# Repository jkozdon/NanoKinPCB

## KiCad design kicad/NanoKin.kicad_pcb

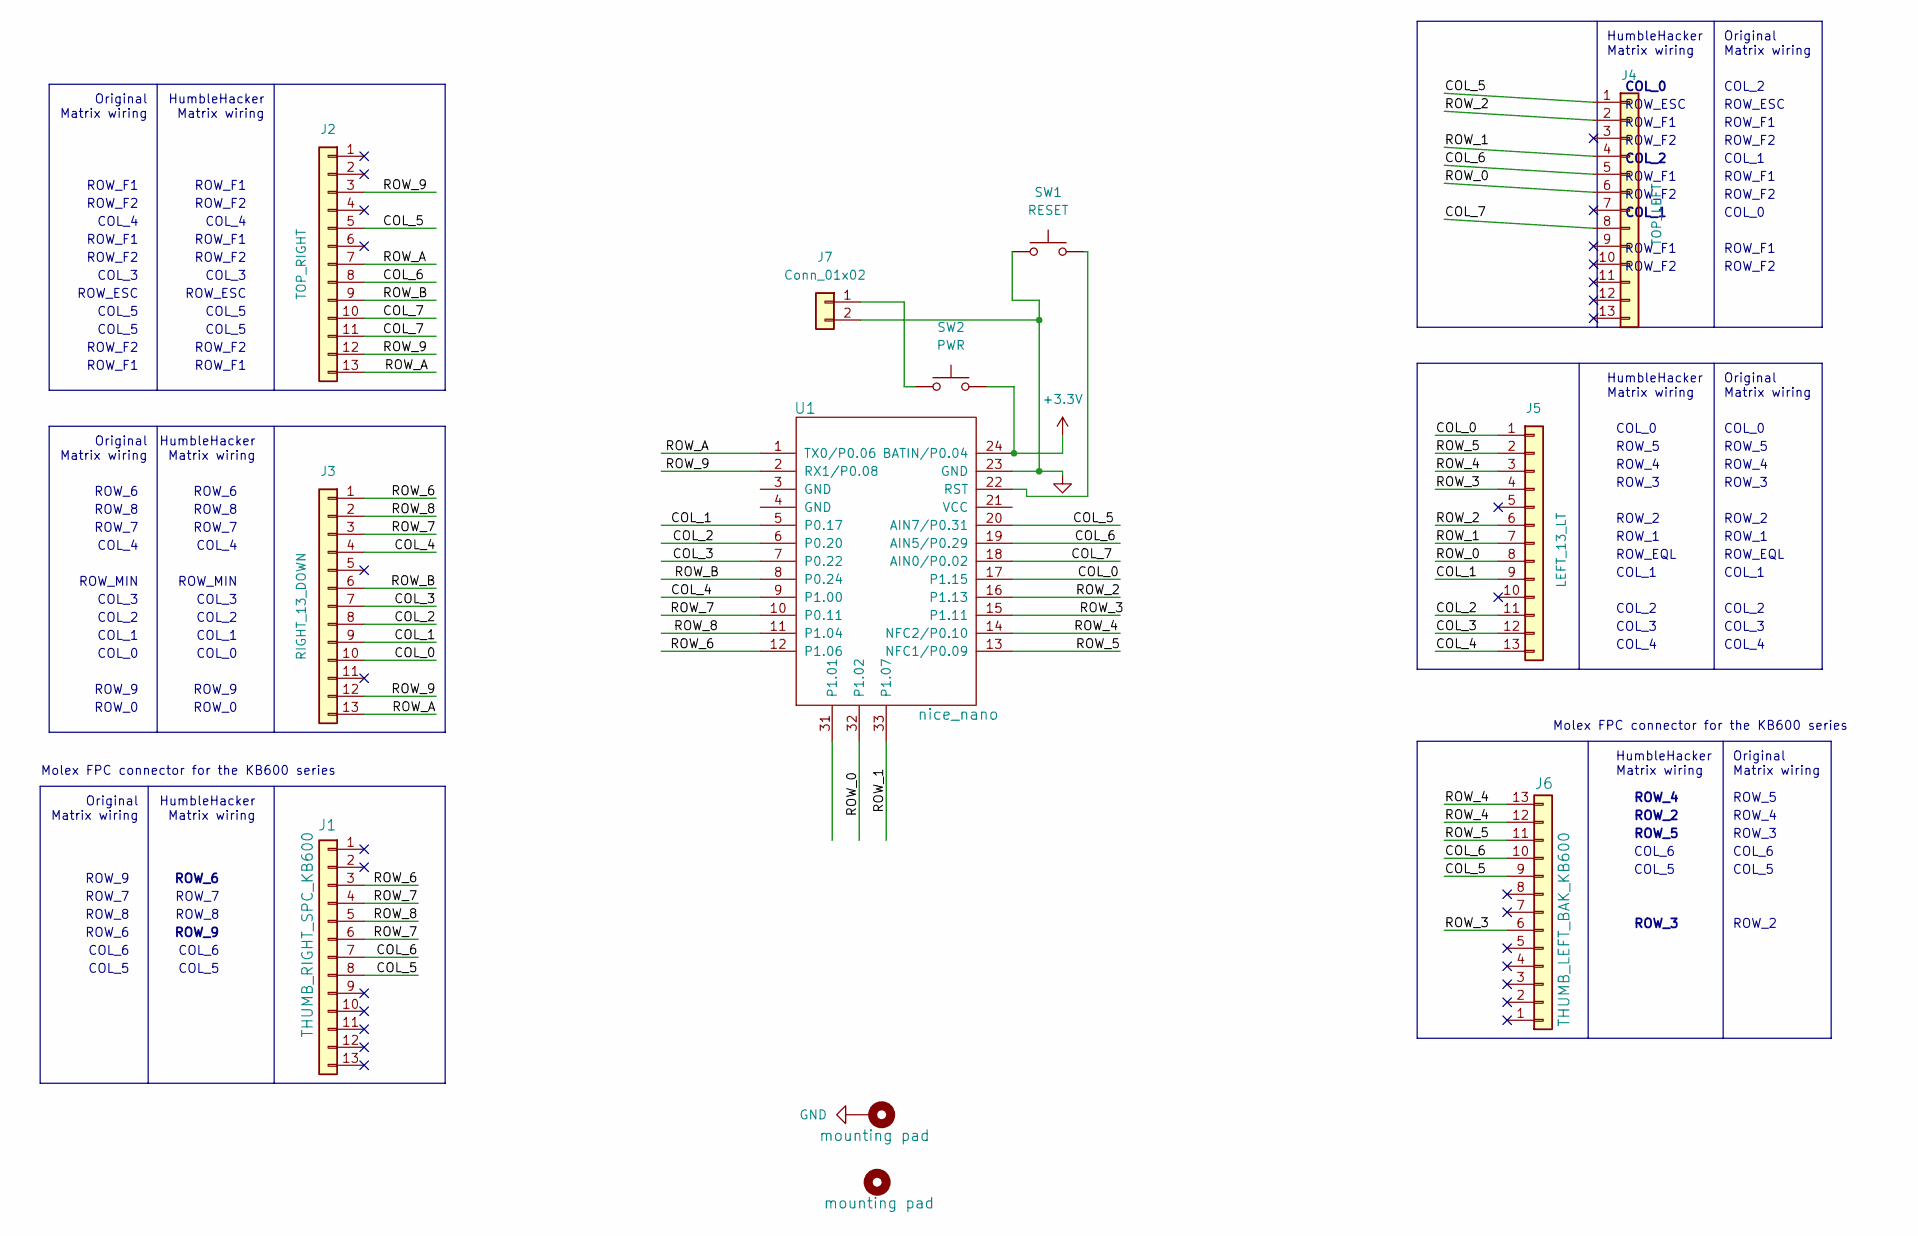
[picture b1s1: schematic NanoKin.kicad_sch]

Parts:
H1: mounting pad; MountingHole_4.3mm_M4_Pad
H2: mounting pad; MountingHole_6mm
J1: THUMB_RIGHT_SPC_KB600; 39-53-2135; MPN 39-53-2135; digikeypn WM14526-ND
J2: TOP_RIGHT; 39-53-2135; MPN 39-53-2135; digikeypn WM14526-ND
J3: RIGHT_13_DOWN; 39-53-2135; MPN 39-53-2135; digikeypn WM14526-ND
J4: TOP_LEFT; 39-53-2135; MPN 39-53-2135; digikeypn WM14526-ND
J5: LEFT_13_LT; 39-53-2135; MPN 39-53-2135; digikeypn WM14526-ND
J6: THUMB_LEFT_BAK_KB600; 39-53-2135; MPN 39-53-2135; digikeypn WM14526-ND
J7: Conn_01x02; bat
SW1: RESET; ResetSW
SW2: PWR; ResetSW
U1: nice_nano

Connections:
+3.3V: SW2.2, U1.24 (BATIN/P0.04)
/COL_0: J3.10, J5.1, U1.17 (P1.15)
/COL_1: J3.9, J5.9, U1.5 (P0.17)
/COL_2: J3.8, J5.11, U1.6 (P0.20)
/COL_3: J3.7, J5.12, U1.7 (P0.22)
/COL_4: J3.4, J5.13, U1.9 (P1.00)
/COL_5: J1.8, J2.5, J4.1, J6.9, U1.20 (AIN7/P0.31)
/COL_6: J1.7, J2.8, J4.5, J6.10, U1.19 (AIN5/P0.29)
/COL_7: J2.10, J2.11, J4.8, U1.18 (AIN0/P0.02)
/ROW_0: J4.6, J5.8, U1.32 (P1.02)
/ROW_1: J4.4, J5.7, U1.33 (P1.07)
/ROW_2: J4.2, J5.6, U1.16 (P1.13)
/ROW_3: J5.4, J6.6, U1.15 (P1.11)
/ROW_4: J5.3, J6.12, J6.13, U1.14 (NFC2/P0.10)
/ROW_5: J5.2, J6.11, U1.13 (NFC1/P0.09)
/ROW_6: J1.3, J3.1, U1.12 (P1.06)
/ROW_7: J1.4, J1.6, J3.3, U1.10 (P0.11)
/ROW_8: J1.5, J3.2, U1.11 (P1.04)
/ROW_9: J2.3, J2.12, J3.12, U1.2 (RX1/P0.08)
/ROW_A: J2.7, J2.13, J3.13, U1.1 (TX0/P0.06)
/ROW_B: J2.9, J3.6, U1.8 (P0.24)
GND: H1.1, J7.2, SW1.1, U1.23 (GND)
unnamed: SW1.2, U1.22 (RST)
unnamed: J7.1, SW2.1

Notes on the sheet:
COL_4
COL_2
COL_6
COL_1
ROW_F2
Original Matrix wiring
ROW_3
ROW_0
ROW_8
COL_3
ROW_2
ROW_F1
ROW_MIN
Molex FPC connector for the KB600 series
ROW_6
COL_5
COL_0
ROW_7
HumbleHacker Matrix wiring
ROW_5
ROW_4
ROW_ESC
ROW_9
ROW_EQL
ROW_1

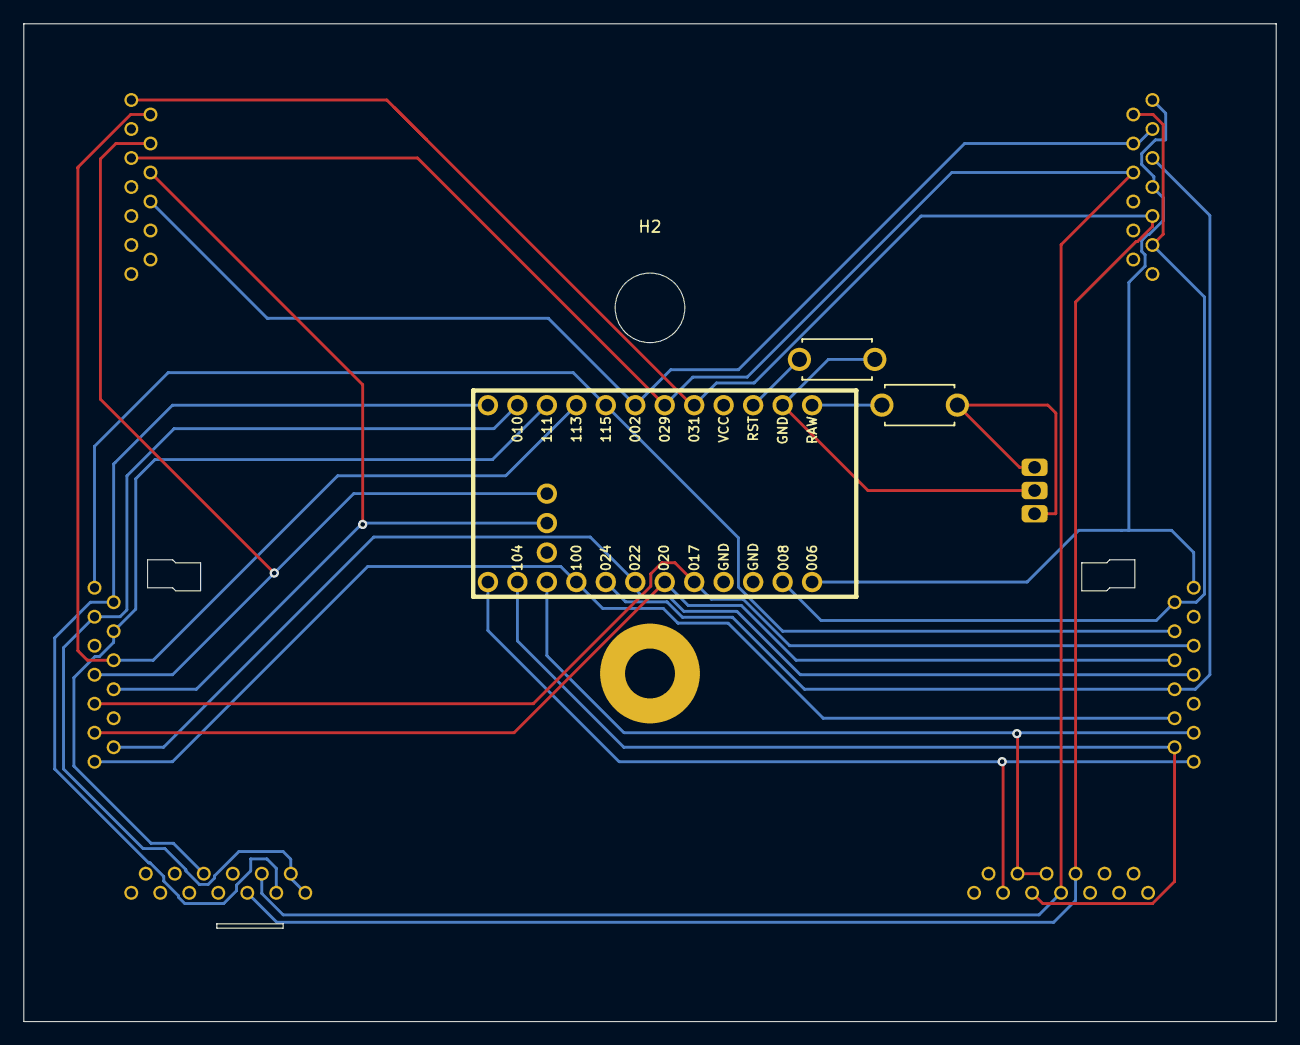
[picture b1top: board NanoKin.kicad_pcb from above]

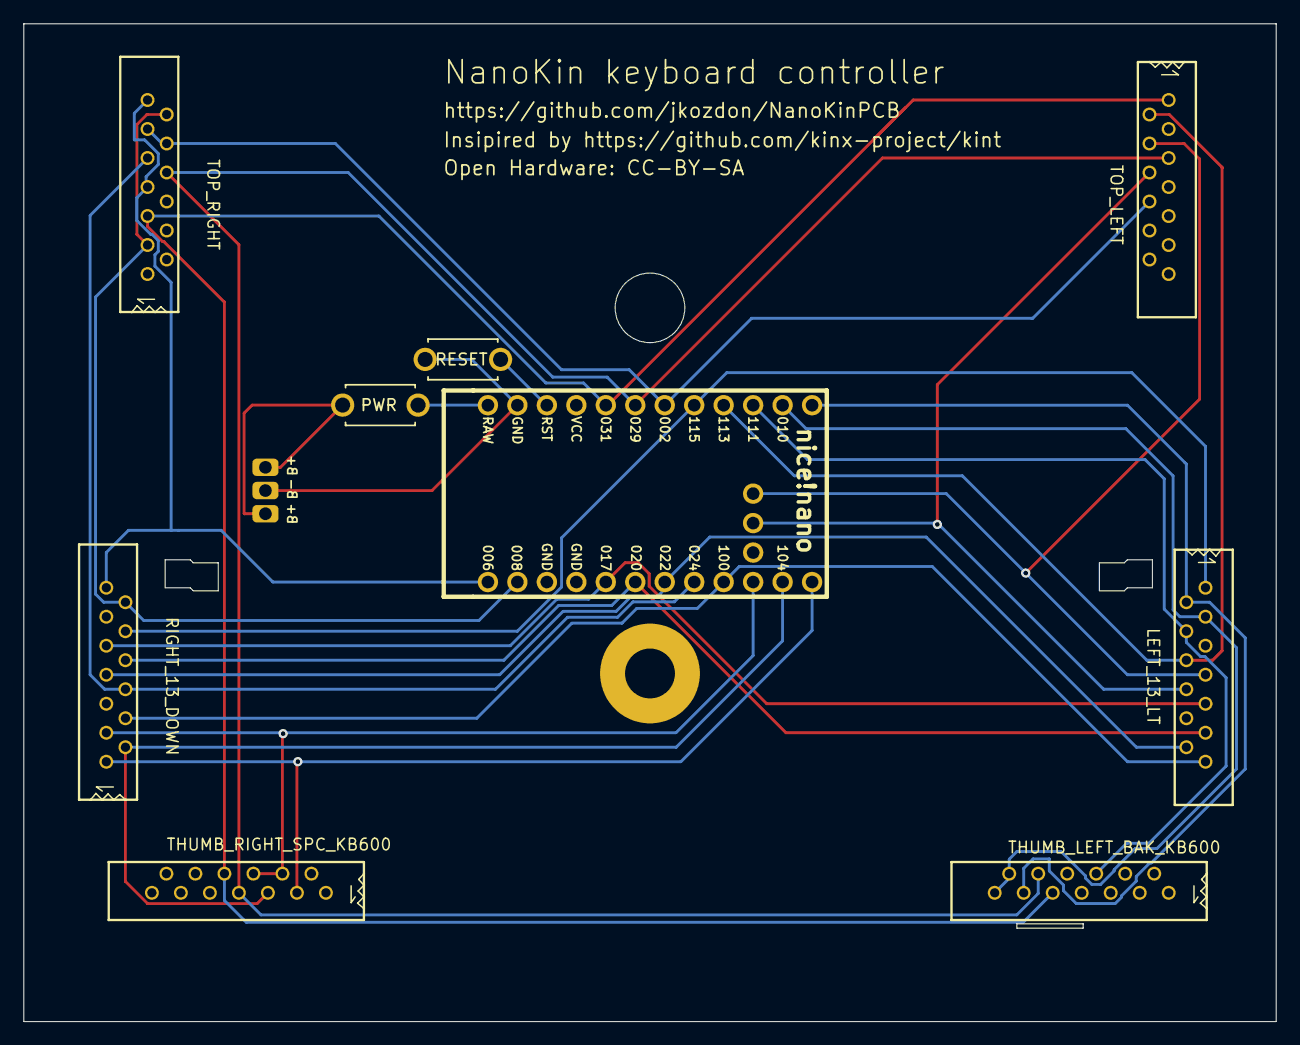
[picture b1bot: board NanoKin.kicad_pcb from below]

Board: 2 copper layers, 107.9 x 86.0 mm, 12 parts (7 on the bottom side), 24 nets.

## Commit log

2022-10-31 Start of NanoKin
2022-10-31 Close to final pin labels
2022-11-07 Routed board
2023-01-29 all files

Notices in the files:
kicad/NanoKin.kicad_pcb:
Open Hardware: CC-BY-SA
